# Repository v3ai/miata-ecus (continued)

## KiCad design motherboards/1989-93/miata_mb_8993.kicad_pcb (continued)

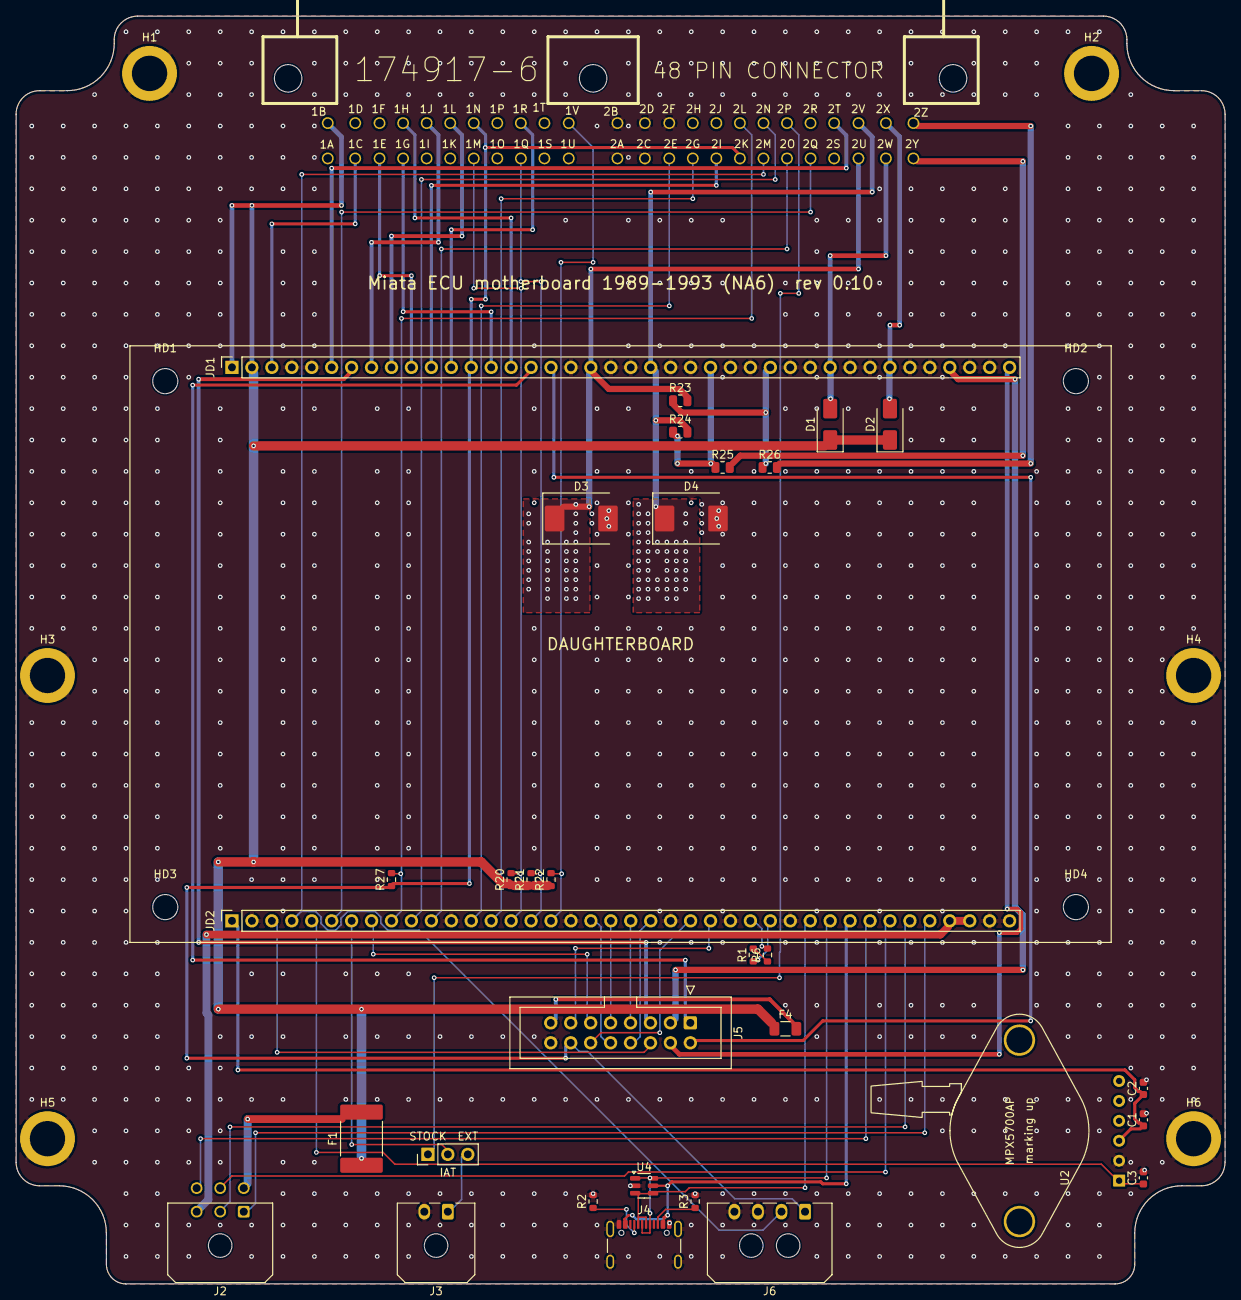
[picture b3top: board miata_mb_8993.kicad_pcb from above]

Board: 2 copper layers, 154.0 x 161.5 mm, 42 parts (0 on the bottom side), 63 nets.

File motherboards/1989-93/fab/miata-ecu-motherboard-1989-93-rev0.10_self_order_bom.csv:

Line,Item,Quantity,Designator,Manufacturer,Manufacture Part Number,LCSC Part Number,Required,Find it,Notes
1,Harness header TE 174917-6,1,J1,TE Connectivity,174917-6,,Yes,https://www.digikey.com/en/products/result?keywords=174917-6,Not available from TE: salvage from a stock NA ECU or buy a clone
2,"Female socket 1x40, 2.54mm, through-hole, 8.5mm",2,"JD1,JD2",Ckmtw(Shenzhen Cankemeng),B-2200S40P-A120,C124412,Yes,https://www.lcsc.com/product-detail/C124412.html,
3,"IDC box header 2x8 (16P), 2.54mm, through-hole",1,J5,BOOMELE(Boom Precision Elec),2.54-2*8P,C3406,Yes,https://www.lcsc.com/product-detail/C3406.html,
4,"Jumper shunt, 2.54 mm",1,,BOOMELE(Boom Precision Elec),2.54 Short Circuit Cap,C5305,Yes,https://www.lcsc.com/product-detail/C5305.html,"For JP1 (IAT source): EXT = board IAT connector J3, STOCK = harness sensor"
5,"Micro-Fit 3.0 header, 1x2 (2P), 3.0mm, right angle, through-hole",1,J3,MOLEX,436500202,C587650,Yes,https://www.lcsc.com/product-detail/C587650.html,
6,"Micro-Fit 3.0 header, 1x4 (4P), 3.0mm, right angle, through-hole",1,J6,MOLEX,436500400,C277684,Yes,https://www.lcsc.com/product-detail/C277684.html,
7,"Micro-Fit 3.0 header, male, 2x3 (6P), 3.0mm, right angle, through-hole",1,J2,MOLEX,430450600,C127367,Yes,https://www.lcsc.com/product-detail/C127367.html,
8,"Pin header, male, 1x3, 2.54mm, through-hole, vertical",1,JP1,BOOMELE(Boom Precision Elec),2.54-1*3PPin,C49257,Yes,https://www.lcsc.com/product-detail/C49257.html,
9,"Pressure sensor 15-700kPa absolute, 5V, ratiometric analog out, unibody single port (867B)",1,U2,NXP,MPX5700AP,C90152,Yes,https://www.lcsc.com/product-detail/C90152.html,"Lies flat, marking side up, leads bent 90 deg down, held by 2 x M3 screws"
10,"Nut, M3",2,,,M3 hex nut,,Yes,,MAP sensor (U2) hold-down
11,"Screw, M3 x 10, pan head",2,,,M3 x 10 pan head,,Yes,,MAP sensor (U2) hold-down
12,"Screw, M3 x 6, pan head",8,,,M3 x 6 pan head,,Yes,,Two per daughterboard standoff (HD1-HD4)
13,"Standoff, M3 x 11 mm, hex, female-female",4,"HD1,HD2,HD3,HD4",,M3 x 11 F-F hex standoff,,Yes,,Daughterboard above the motherboard (8.5 mm sockets + 2.5 mm header plastic)
14,Thick film resistor 0 ohm 0805,2,"R25,R26",UNI-ROYAL(Uniroyal Elec),0805W8F0000T5E,C17477,Optional,https://www.lcsc.com/product-detail/C17477.html,"R25: sequential conversion only, INJ3 to 2Y (fit instead of R24); R26: sequential conversion only, INJ4 to 2Z (fit instead of R23). NEVER on an automatic: 2Z is the A/T unit"
15,Thick film resistor 4.7k 1% 100mW 0603,4,"R20,R21,R22,R27",UNI-ROYAL(Uniroyal Elec),0603WAF4701T5E,C23162,Optional,https://www.lcsc.com/product-detail/C23162.html,"R20: 12 V pull-up for the vehicle speed input. Fit (4.7k 0603, LCSC C23162: 48 mW at 15 V with the switch closed) only if your car's signal switches to ground or is open collector; a switch that drives 12 V must not have it; R21: 12 V pull-up for the A/C switch input. Fit (4.7k 0603, LCSC C23162: 48 mW at 15 V with the switch closed) only if your car's signal switches to ground or is open collector; a switch that drives 12 V must not have it; R22: 12 V pull-up for the clutch switch input. Fit (4.7k 0603, LCSC C23162: 48 mW at 15 V with the switch closed) only if your car's signal switches to ground or is open collector; a switch that drives 12 V must not have it; R27: 5 V pull-up for the TPS idle switch on 2L (manual cars). Fit (4.7k 0603, LCSC C23162; 1.1 mA with the switch closed) if the idle switch is used; from the protected harness 5 V"
16,"Throttle position sensor, 0-5 V potentiometer, 3 pins",1,,Bosch,0 280 122 001,,Manual cars,https://www.digikey.com/en/products/result?keywords=0%20280%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,"Same part as BMW 13 63 1 721 456; the sensor the NA6 adapter plates below are made for. 86 deg usable travel, 2 kOhm track, -40 to +130 C. Pins 1 and 2 are the ends of the track (5 V and ground, about 2 kOhm between them at any throttle), pin 3 the wiper (signal): check with an ohmmeter before wiring. Replaces the stock idle switch"
17,TPS adapter plate for the NA6 throttle body (buy),1,,Flyin' Miata,"TPS upgrade kit 07-360XX, no-TPS option",,Manual cars,https://flyinmiata.com/products/tps-upgrade,Bolts to the side of the 1990-93 manual throttle body and carries the Bosch / BMW sensor. Either this or the printed plate below. Not with an NB intake manifold
18,"TPS plug, Bosch Junior Timer 3-pin, with terminals",1,,Bosch,1 237 000 039,,Manual cars,https://www.efihardware.com/products/388/connector-TPS-Modul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,Mates with the Bosch 0 280 122 001. Buy it as a kit with its terminals (e.g. EFI Hardware C03F-0002): loose terminals often don't fit the housing
19,"Shielded cable, 3 x 22 AWG with drain, 105 C or better",3,,,"M27500-22SB3T23 (or equivalent), metres",,Manual cars,,J6 to the sensor: about 3 m from the ECU in the passenger footwell through the firewall to the throttle body; measure your route. Shield drain to J6 pin 4 only (open at the sensor end). Office cable rated 60 C is not good enough under the hood. Three twisted 22 AWG TXL wires in loom also work (leave pin 4 empty)
20,"Micro-Fit 3.0 receptacle, 1x4",1,,Molex,43645-0400,,Manual cars,https://www.digikey.com/en/products/result?keywords=43645-0400,"Mates with J6: 1 = 5 V, 2 = TPS signal, 3 = sensor ground, 4 = shield drain"
21,"Micro-Fit 3.0 female crimp terminal, 20-24 AWG (TPS lead)",4,,Molex,43030-0007,,Manual cars,https://www.digikey.com/en/products/result?keywords=43030-0007,For the J6 receptacle; buy spares
22,TPS adapter plate for the NA6 throttle body (3D print),1,,,Thingiverse 4476762 or Printables 619337,,Optional,https://www.thingiverse.com/thing:4476762,"Instead of the bought plate: Skuzzle's ""Mazda MX5 - BMW TPS adapter"" (Thingiverse 4476762), or its thicker remix ""BMW tps adaptor maximum beef"" (Printables 619337). Print in ASA (PLA and PETG soften in the engine bay); check the licence on the model page"
23,"Screw, M4, with nut (sensor to printed plate)",2,,,"M4 screw + M4 nut, length to suit the plate",,Optional,,Printed plate only
24,"Screw, M4, with wide (fender) washer (printed plate to throttle body)",2,,,"M4 screw + M4 fender washer, length to suit",,Optional,,Printed plate only: the wide washers spread the load on the plastic
25,"Convoluted loom, 6 mm (1/4 in), split",2,,,"6 mm split loom, metres",,Optional,,"Engine-bay run of the TPS lead; tie it to the engine harness, away from the exhaust and the coil leads"

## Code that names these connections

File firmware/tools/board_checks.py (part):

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Datasheet limits used (STM32F407 DS8626, STM32F103x8 DS5319; F4 family IINJ table re-confirmed in the STM32F412
datasheet, same structure):
  FT pins: VIN abs max VDD + 4.0 V; injected current -5 / +0 mA (no positive injection possible: there is no clamp
  to VDD, so the limit above VDD is the voltage, not a current). TTa (PA4/PA5) and F103 non-FT pins: VIN abs max
  4.0 V, injected current +-5 mA (diodes to VDDA / VDD). Total injected current +-25 mA. Operating range on FT pins
  -0.3..5.5 V. An FT pin used as an ADC input is treated as good to VDDA only (outside it the reading clips; tolerance
  above VDDA in analog mode is not relied on: CHECK).
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F407_NAME = {int(n): name for n, name in
             (s.split(':') for s in open(os.path.join(SCRIPTS, 'stm32f407v_lqfp100_pins.txt')).read().split())}
F407_PIN = {v: k for k, v in F407_NAME.items()}
# DS8626 pin definitions, LQFP100: every GPIO is FT except PA4/PA5 (TTa, DAC outputs); PC13-15 are FT but sit in the
# backup domain (2 MHz, 3 mA total sink/source through the power switch).
F407_TTA = {'PA4', 'PA5'}
F103_NAME = {1: 'VBAT', 2: 'PC13', 3: 'PC14', 4: 'PC15', 5: 'PD0', 6: 'PD1', 7: 'NRST', 8: 'VSSA', 9: 'VDDA',
             10: 'PA0', 11: 'PA1', 12: 'PA2', 13: 'PA3', 14: 'PA4', 15: 'PA5', 16: 'PA6', 17: 'PA7', 18: 'PB0',
             19: 'PB1', 20: 'PB2', 21: 'PB10', 22: 'PB11', 23: 'VSS', 24: 'VDD', 25: 'PB12', 26: 'PB13', 27: 'PB14',
             28: 'PB15', 29: 'PA8', 30: 'PA9', 31: 'PA10', 32: 'PA11', 33: 'PA12', 34: 'PA13', 35: 'VSS', 36: 'VDD',
             37: 'PA14', 38: 'PA15', 39: 'PB3', 40: 'PB4', 41: 'PB5', 42: 'PB6', 43: 'PB7', 44: 'BOOT0', 45: 'PB8',
             46: 'PB9', 47: 'VSS', 48: 'VDD'}
# DS5319 pin definitions: FT = PA8-PA15, PB2-PB4, PB6-PB15, PD0/PD1; not FT: PA0-PA7, PB0, PB1, PB5, PC13-PC15
F103_FT = {'PA8', 'PA9', 'PA10', 'PA11', 'PA12', 'PA13', 'PA14', 'PA15', 'PB2', 'PB3', 'PB4', 'PB6', 'PB7', 'PB8',
           'PB9', 'PB10', 'PB11', 'PB12', 'PB13', 'PB14', 'PB15', 'PD0', 'PD1'}
VDD = 3.3
LIM_FT_V = VDD + 4.0          # abs max on FT pins
LIM_NONFT_V = 4.0             # abs max on TTa / non-FT pins
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FT_OPER_MAX = 5.5
VIL, VIH = 0.3 * VDD, 0.7 * VDD   # DS8626 CMOS levels (conservative; FT inputs switch at 1.79 V by design)

ADC = {**{f'EFI_ADC_{i}': f'PA{i}' for i in range(8)}, 'EFI_ADC_8': 'PB0', 'EFI_ADC_9': 'PB1',
       **{f'EFI_ADC_{10 + i}': f'PC{i}' for i in range(6)}}

# alternate functions whose direction matters (DS8626 / DS5319 alternate-function tables)
AF_DIR = {('U1', 'PB12'): ('CAN2_RX', 'in'), ('U1', 'PB13'): ('CAN2_TX', 'out'),
          ('U1', 'PC6'): ('USART6_TX', 'out'), ('U1', 'PC7'): ('USART6_RX', 'in'),
          ('U1', 'PD8'): ('USART3_TX', 'out'), ('U1', 'PD9'): ('USART3_RX', 'in'),
          ('U102', 'PA9'): ('USART1_TX', 'out'), ('U102', 'PA10'): ('USART1_RX', 'in'),
          ('U102', 'PA11'): ('CAN_RX', 'in'), ('U102', 'PA12'): ('CAN_TX', 'out')}


def mcu_pin_info(ref, pad):
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    'vehicleSpeedSensorInputPin': 'vss', 'acSwitch': 'acSwitch', 'clutchDownPin': 'clutch',
    'tps1_1AdcChannel': 'tps', 'mafAdcChannel': 'maf', 'afr.hwChannel': 'afr', 'ignKeyAdcChannel': 'ignKey',
    'vbattAdcChannel': 'vbatt', 'clt.adcChannel': 'clt', 'iat.adcChannel': 'iat', 'map.sensor.hwChannel': 'map',
    'canTxPin': 'can2Tx', 'canRxPin': 'can2Rx',   # PB13/PB12 = CAN2 peripheral, rusEFI's first bus
}
FW_OUTPUTS = {'ign1&4', 'ign3(COP)', 'ign2&3', 'ign4(COP)', 'inj1', 'inj2', 'inj3', 'inj4', 'idle', 'fuelPump',
              'acRelay', 'fan', 'fan2', 'cel', 'tach', 'boost', 'mainRelay', 'alternator', 'vvt', 'o2heater'}
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    wb = open(os.path.join(BOARD, 'wideband_uart_flash.cpp')).read()
    for label, port in re.findall(r'efiSetPadMode\("WBO ([\w ]+)", Gpio::(\w+)', wb):
        board['wbo ' + label] = 'P' + port
    board['usbDM'], board['usbDP'], board['swdio'], board['swclk'] = 'PA11', 'PA12', 'PA13', 'PA14'
    board['uart6Tx'], board['uart6Rx'] = 'PC6', 'PC7'   # rusEFI's TS secondary / AUX UART (J5-12/13)
    return out, board, sorted(external)


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                      'o2heater', 'vvt', 'boost', 'vss', 'acSwitch', 'clutch'):
                fw[k] = kv.get(k, '-')
            fw = {k: ('P' + v if not v.startswith('P') else v) for k, v in fw.items() if v not in ('-', '')}
            if kv.get('ignKey', '-') not in ('-', ''):      # the dump names the ADC channel ("VIGN"), which is PA2
                fw['ignKey'] = 'PA2'
            out[parts[1]] = fw
    return out

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        row('FAIL', 'mating', year, f'{mb_path}: ' + '; '.join(bad[:6]))
    else:
        row('OK', 'mating', year, f'{mb_path}: all {len(dj)} J1/J2 pads land on JD1/JD2 by pure translation '
            f'({ox:.2f}, {oy:.2f} mm), same pin and net (HTR_GND -> motherboard GND by design)')


# ------------------------------------------------------------------------------------------------------------------
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    has_key = 'ignKey' in fw
    want = exp_tab.get('ignKey')
    ok = (has_key and want in vign_cav) or (not has_key and not want)
    row('OK' if ok else 'FAIL', 'reverse', year, f'ignition sense {"PA2 (AN_VIGN)" if has_key else "not configured"}; '
        f'VIGN_IN cavities wired {vign_cav or "-"}; reference {want or "none"}')
    # unused F407 GPIO with a harness path but no firmware function (informational)
    for pad, net in sorted(sysm.by_ref['U1']['pads'].items(), key=lambda kv: int(kv[0])):
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    """two drivers on one net (push-pull + anything, open drain + car output); intentional open-drain pairs."""
    res = research.get(RESEARCH_YEAR.get(year, ''), {})
    out_ports = {p for f, p in fw.items() if f in FW_OUTPUTS} | {board_fw[k] for k in board_fw if k.startswith('led')} \
        | {board_fw['wbo BOOT0'], 'PB13', 'PC6', 'PD8'}
    od_ports = {board_fw['drvEnable'], board_fw['wbo NRST']}
    drv = collections.defaultdict(list)    # net -> [(who, kind)]  kind: pp / od
    for p in sysm.parts:
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                    drv[net].append((f'U1 {name}', 'pp'))
            elif ref == 'U102':
                name = mcu_pin_info('U102', pad)[0]
                if name in ('PA6', 'PB10', 'PB5', 'PB6', 'PB7', 'PB8', 'PB9', 'PA9', 'PA12'):
                    drv[net].append((f'U102 {name}', 'pp'))
            elif val == 'ULN2003AD' and pad in ('10', '11', '12', '13', '14', '15', '16'):
                drv[net].append((f'{ref}.{pad}', 'od'))
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                   '5': ('+5V', 'ADJ reference')},
    'LMR14020': {'3': ('+12V_F', 'EN (tie to VIN or divider)'), '7': ('GND', 'GND'), '9': ('GND', 'exposed pad')},
    'SN74LVC4245APWR': {'2': ('GND', 'DIR: low = B->A'), '22': ('DRV_EN_N', 'OE')},
    'STM32F407VGT6': {'94': ('BOOT0', 'BOOT0 pulled down'), '37': ('BOOT1', 'PB2/BOOT1 pulled down'),
                      '20': ('GND', 'VSSA'), '21': ('+3V3A', 'VREF+'), '22': ('+3V3A', 'VDDA'),
                      '49': ('VCAP1', 'VCAP1'), '73': ('VCAP2', 'VCAP2'), '6': ('+3V3', 'VBAT')},
    'STM32F103C8T6': {'1': ('+3V3', 'VBAT'), '8': ('GND', 'VSSA'), '9': ('WB_VDDA', 'VDDA'), '44': ('WB_BOOT0', 'BOOT0'),
                      '20': ('WB_BOOT1', 'PB2/BOOT1')},
    'SN65HVD230DR': {'8': ('GND', 'Rs: GND = high speed (open would be standby? low-power mode)')},
    'TCAN1042VDRQ1': {'3': ('+5V', 'VCC 4.5-5.5 V'), '5': ('+3V3', 'VIO = MCU I/O level'),
                      '8': ('GND', 'STB: low = normal mode (internal pull-up would select standby)'), '2': ('GND', 'GND')},
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    ('LM2903DR', ['2', '3', '5', '6'], 'LM2903 input', True, 'unused VR channel must sit at a defined level'),
    ('LMV321IDBVR', ['1', '3'], 'LMV321 input', True, 'knock amp bias'),
    ('STM32F407VGT6', ['94', '37'], 'F407 BOOT0/BOOT1', True, 'boot mode'),
    ('STM32F103C8T6', ['44', '20'], 'F103 BOOT0/BOOT1', True, 'boot mode (BOOT0 is driven by the F407 PD10, high-Z in reset)'),
]


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        relay = [c for c, n in sysm.cavity.items() if n == 'OUT_MAINRLY' and c not in year_unwired(year)]
        txt = f'ignition wake: {vi} -> D8 -> F1: +12V {V["+12V"]:.2f} V with the main relay open'
        if hold:
            txt += f'; firmware holds the main relay on {relay} ({hold}) and reads the key on PA2'
        row('OK' if V['+12V'] > 12 else 'FAIL', 'power', year, txt)
    elif fw.get('mainRelay'):
        row('FAIL', 'power', year, 'firmware drives a main relay but no ignition wake cavity is wired')
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    dc.fix('_HALF', 1.65)
    dc.fix('_MAP', 0.85)
    out_ports = {p for f, p in fw.items() if f in FW_OUTPUTS} | {board_fw[k] for k in board_fw if k.startswith('led')} \
        | {board_fw['wbo BOOT0'], 'PB13', 'PC6', 'PD8'}
    for p in sysm.parts:
        ref, val, pads, fp = p['ref'], p['value'], p['pads'], p['fp']
        base = ref.split('.')[-1]
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                    dc.d(net, vdd, 0.5, 10, tag=('MCU+', ref, k))
                if ref == 'U1' and name in out_ports:
                    dc.r(net, '+3V3' if states.get(f'U1.{name}') == 'high' else 'GND', 40, tag=('MCU_OUT', ref, k))
                if ref == 'U102' and name == 'PB10':
                    dc.r(net, 'GND', 40)
                if ref == 'U102' and name == 'PA6':
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
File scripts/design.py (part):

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J1 = {1: 'VBAT_IN', 2: 'VBAT_IN', 3: 'VIGN_IN', 4: 'GND', 5: 'GND',
      6: 'OUT_FP', 7: 'OUT_MAINRLY', 8: 'OUT_AC', 9: 'OUT_FAN', 10: 'OUT_CEL',
      11: 'OUT_TACH', 12: 'OUT_LS7',
      # rev 0.8: pin 13 (was GND) carries the harness sensor 5 V (V5_EXT, its own protected tracker U14), so a
      # harness 5 V wire shorted to battery no longer back-feeds the on-board MAP sensor (V5_SENS, J2-1)
      13: 'V5_EXT',
      14: 'OUT_IGN1', 15: 'OUT_IGN2', 16: 'OUT_IGN3', 17: 'OUT_IGN4', 18: 'GND'}
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    '21': '+3V3A', '22': '+3V3A',
    '49': 'VCAP1', '73': 'VCAP2',
    '12': 'HSE_IN', '13': 'HSE_OUT', '14': 'NRST', '94': 'BOOT0',
    # relay/lamp outputs from the top of the left edge (ULN2003 sits up-left). PC13/PC14 run through the backup
    # power switch, which can supply 3 mA in total; the two ULN2003 inputs draw at most ~0.72 mA each at 3.3 V
    # ((3.3 - 2 Vbe) / 2.7k), so 1.45 mA together, and relays need no speed (ST's limit there is 2 MHz).
    '1': 'LS7_CTL', '2': 'TACH_CTL', '3': 'CEL_CTL', '4': 'FAN_CTL', '5': 'AC_CTL',
    '7': 'MAINRLY_CTL', '8': 'FP_CTL',
    # rev 0.5: PB2 is BOOT1; pulled low so ST's DFU bootloader starts reliably (BOOT0 = 1, BOOT1 = 0)
    '37': 'BOOT1',
    # rev 0.5: low-side driver enable (PA8, active low, pulled up to +5V: drivers off until firmware enables).
    # On the right edge, so it reaches U11's ~OE from below instead of adding a ninth line to the top-edge bundle.
    '67': 'DRV_EN_N',
    # ignition + smart low sides from the top edge, ordered left->right like the driver row
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    '93': 'INJ1_CTL', '92': 'INJ2_CTL', '91': 'INJ3_CTL', '90': 'INJ4_CTL',
    '89': 'IACV_CTL', '88': 'VVT_CTL', '87': 'BOOST_CTL', '86': 'ALT_CTL',
    # analog: all nine sensor inputs on the bottom edge in J2 column order, knock on
    # PA3 (ADC3_IN3); battery/ignition sense on the left edge next to their divider
    '26': 'AN_KNOCK', '29': 'AN_TPS', '30': 'AN_MAP', '31': 'AN_CLT', '32': 'AN_IAT',
    '33': 'AN_AFR', '34': 'AN_AUX1', '35': 'AN_AUX2', '36': 'AN_AUX3',
    '24': 'AN_VBATT', '25': 'AN_VIGN',
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    '38': 'HALL1', '39': 'HALL2', '40': 'SW1', '41': 'SW2', '42': 'SW3',
    '43': 'VR2_OUT', '44': 'VR1_OUT',
    # comms (right edge)
    '51': 'CAN_RX', '52': 'CAN_TX',            # CAN2 PB12/PB13
    # rev 0.10: PC6 / PC7 are the flex-fuel sensor and nitrous arming inputs (they were a spare UART); same 10k + clamps
    '63': 'FLEX_M', '64': 'N2O_ARM_M',
    # rev 0.10: microSD on SPI2 (PB10 SCK, PB14 MISO, PB15 MOSI; CS on PD13)
    '47': 'SD_SCK', '53': 'SD_MISO', '54': 'SD_MOSI', '60': 'SD_CS',
    # LEDs: run PD12, error PD15; rev 0.8 moved comms and warning to PC8/PC9 (PD13/PD14 left no route to the LED column)
    '59': 'LED_RUN', '65': 'LED_COMM', '66': 'LED_WARN', '62': 'LED_ERR',
    # wideband MCU programming link (rev 0.4): USART3 on PD8/PD9 to the wideband MCU's ROM-bootloader USART1 (F103 since rev 0.6)
    # (PA10/PA9), PD10 drives its BOOT0 (10k pull-down stays), PD11 (open drain) its NRST
    '55': 'WB_PROG_TX', '56': 'WB_PROG_RX', '57': 'WB_BOOT0', '58': 'WB_NRST',
    '70': 'USB_DM', '71': 'USB_DP',            # OTG_FS PA11/PA12
    '72': 'SWDIO', '76': 'SWCLK',              # PA13/PA14
}
add('U1', 'STM32F407VGT6', 'LQFP100', 'C12345', mcu, 'MCU, 168MHz Cortex-M4F, 1MB flash')

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    R(f'R{rn}', '10k', 'AN_' + n, 'GND', '0402'); rn += 1
    C(f'C{cn}', '10n', 'AN_' + n, 'GND', '0402'); cn += 1
    if n in ('CLT', 'IAT'):     # rev 0.8: bias from the harness sensor supply V5_EXT (the sensors are harness parts)
        R(f'R{rn}', '2.7k', 'V5_EXT', 'IN_' + n, '0603'); rn += 1

# knock: AC coupled, biased to 1.65V, gain 5.7. Rev 0.7: the coupling cap follows R138 (2.2k, see the rev 0.7 block)
C(f'C{cn}', '100n', 'KN_IN', 'KN_P'); cn += 1
R(f'R{rn}', '100k', 'KN_P', 'KN_BIAS'); rn += 1
R(f'R{rn}', '100k', '+3V3', 'KN_BIAS'); rn += 1
R(f'R{rn}', '100k', 'KN_BIAS', 'GND'); rn += 1
C(f'C{cn}', '1u', 'KN_BIAS', 'GND'); cn += 1
R(f'R{rn}', '47k', 'KN_OUT', 'KN_N'); rn += 1
R(f'R{rn}', '10k', 'KN_N', 'KN_BIAS'); rn += 1
R(f'R{rn}', '330', 'KN_OUT', 'AN_KNOCK'); rn += 1
C(f'C{cn}', '10n', 'AN_KNOCK', 'GND'); cn += 1
C(f'C{cn}', '100n', '+3V3', 'GND'); cn += 1
add('U8', 'LMV321IDBVR', 'SOT235', 'C7972',
    {'1': 'KN_P', '2': 'GND', '3': 'KN_N', '4': 'KN_OUT', '5': '+3V3'}, 'knock amp')
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# 2 x 5.1k to the comparator inputs, 1 nF across them, a BAT54S on each input to GND and +5V (holds them at -0.3..5.3 V;
# the LM2903 inputs take up to 36 V and down to -0.3 V), 100k from each input to VBIAS (1.65 V), and 1M from the
# open-collector output back to IN+ for about 30 mV of hysteresis. Output high when harness - is above harness +
# (the MAX9926's polarity), 10k pull-up to +3V3 into PE13/PE12. See firmware/tools/circuit_sim.py section H.
# comparator A (pins 1-3) takes VR2 and B (5-7) VR1, so each channel's pins face its own header columns
add('U9', 'LM2903DR', 'SOIC8', 'C7549',
    {'1': 'VR2_OUT', '2': 'VR2_INN', '3': 'VR2_INP', '4': 'GND',
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    R(f'R{rn}', '4.7k', 'IN_' + n, n, '0603'); rn += 1
    R(f'R{rn}', '1k', f'V5_H{k + 1}', 'IN_' + n, '0603'); rn += 1
    C(f'C{cn}', '1n', n, 'GND', '0402'); cn += 1
# rev 0.5: clamp diodes to +3V3 (PE7/PE8 are 5 V-tolerant pins with no clamp of their own; a crank/cam wire
# shorted to battery would otherwise put ~14 V on them). 4.7k limits the clamp current to ~2 mA.
add('D13', '1N4148WS', 'SOD323', 'C2128', {'1': '+3V3', '2': 'HALL1'}, 'HALL1 clamp to +3V3')
add('D14', '1N4148WS', 'SOD323', 'C2128', {'1': '+3V3', '2': 'HALL2'}, 'HALL2 clamp to +3V3')
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C('C57', '100n', '+5V', 'GND', '0402')        # U11 VCCA
C('C58', '100n', '+3V3', 'GND', '0402')       # U11 VCCB
R('R71', '10k', '+5V', 'DRV_EN_N', '0402')    # drivers disabled until the firmware pulls DRV_EN_N low
R('R72', '10k', 'BOOT1', 'GND', '0402')       # PB2 / BOOT1 low
# The MCU-side control lines have no pull-downs (no room between the MCU and U11). While U11 is disabled its
# outputs are high-impedance and R19-R26 hold the drivers off, so a floating MCU pin does nothing. Once enabled,
# the board firmware parks every control pin rusEFI isn't using as an input with pull-down (rusEFI's own
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# AUX header UART (J2 24/25 -> motherboard J5): 10k in series and a BAT54S clamp at the MCU side, so the header pins
# survive car wiring shorted to battery (about 55 mW in the resistor at 24 V; 4.7k took 120 mW, over the 0603's 100 mW);
# 10k + ~50 pF of header and cable is 0.5 us, fine at 115200 baud (8.7 us per bit)
# Rev 0.10: the two pins are general 0-12 V digital inputs now: flex-fuel sensor (PC6, EXTI line 6 is free; PC7 would
# share line 7 with the crank input on PE7) and the nitrous arming switch (PC7, polled). Pull-ups are on the motherboard.
R('R139', '10k', 'FLEX_M', 'IN_FLEX')
R('R140', '10k', 'N2O_ARM_M', 'IN_N2O')
add('D36', 'BAT54S', 'SOT23', 'C19726', {'1': 'GND', '2': '+3V3', '3': 'FLEX_M'}, 'flex input clamp')
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R('R161', '47k', '+3V3', 'SD_MOSI', '0402')
R('R162', '47k', '+3V3', 'SD_DAT1', '0402')
R('R163', '47k', '+3V3', 'SD_DAT2', '0402')
# battery / ignition sense clamps: in a 24 V jump start the divider put 4.0 V on PA1 (analog mode, VDDA + 0.3 V max)
add('D38', 'BAT54WS', 'SOD323', 'C124205', {'1': '+3V3', '2': 'AN_VBATT'}, 'AN_VBATT clamp to +3V3')
add('D39', 'BAT54WS', 'SOD323', 'C124205', {'1': '+3V3', '2': 'AN_VIGN'}, 'AN_VIGN clamp to +3V3')
# +3V3 shunt clamp: every clamp on the board (analog, hall, switch, UART, the wideband's pump/Vm drive) dumps a fault
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
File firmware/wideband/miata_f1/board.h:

/*
    ChibiOS - Copyright (C) 2006..2018 Giovanni Di Sirio

    Licensed under the Apache License, Version 2.0 (the "License");
    you may not use this file except in compliance with the License.
    You may obtain a copy of the License at

        http://www.apache.org/licenses/LICENSE-2.0

    Unless required by applicable law or agreed to in writing, software
    distributed under the License is distributed on an "AS IS" BASIS,
    WITHOUT WARRANTIES OR CONDITIONS OF ANY KIND, either express or implied.
    See the License for the specific language governing permissions and
    limitations under the License.
*/

#ifndef _BOARD_H_
#define _BOARD_H_

/*
 * Board identifier.
 */
#define BOARD_NAME                  "miata-ecus daughterboard wideband (STM32F103C8)"

/*
 * Board oscillators-related settings.
 * NOTE: LSE not fitted.
 * HSE: 8 MHz crystal Y101.
 */
#if !defined(STM32_LSECLK)
#define STM32_LSECLK                0U
#endif

#if !defined(STM32_HSECLK)
#define STM32_HSECLK                8000000U
#endif

/*
 * MCU type: STM32F103C8T6 / CBT6 (medium density, 64/128 KB flash, 20 KB RAM, LQFP48).
 */
#define STM32F103xB

/*
 * I/O ports initial setup, this configuration is established soon after reset
 * in the initialization code.
 *
 * The digits have the following meaning:
 *   0 - Analog input.
 *   1 - Push Pull output 10MHz.
 *   2 - Push Pull output 2MHz.
 *   3 - Push Pull output 50MHz.
 *   4 - Digital input.
 *   5 - Open Drain output 10MHz.
 *   6 - Open Drain output 2MHz.
 *   7 - Open Drain output 50MHz.
 *   8 - Digital input with PullUp or PullDown resistor depending on ODR.
 *   9 - Alternate Push Pull output 10MHz.
 *   A - Alternate Push Pull output 2MHz.
 *   B - Alternate Push Pull output 50MHz.
 *   C - Reserved.
 *   D - Alternate Open Drain output 10MHz.
 *   E - Alternate Open Drain output 2MHz.
 *   F - Alternate Open Drain output 50MHz.
 * Please refer to the STM32 Reference Manual for details.
 */

/*
 * Port A setup (the analog front end is the rusEFI/FOME wideband module, rev C).
 * PA0  - Un_sense (Nernst, x2.7)   (analog in, ADC12_IN0).
 * PA1  - not connected (rev 0.7; the module wired it to LSU_Vm, never sampled).
 * PA2  - Ip_sense                  (analog in, ADC12_IN2).
 * PA3  - Vm_sense (virtual ground) (analog in, ADC12_IN3).
 * PA4, PA5 - unused                (input, pull-up).
 * PA6  - Ip_dac PWM, TIM3_CH1      (alternate pushpull, 50 MHz).
 * PA7, PA8 - unused                (input, pull-up).
 * PA9  - USART1_TX                 (input, pull-up: only the ROM bootloader uses it, for flashing from the ECU).
 * PA10 - USART1_RX                 (input, pull-up).
 * PA11 - CAN_RX                    (input, pull-up).
 * PA12 - CAN_TX                    (alternate pushpull, 50 MHz).
 * PA13 - SWDIO, PA14 - SWCLK, PA15 - unused (JTDI).
 */
#define VAL_GPIOACRL            0x8B880000      /*  PA7...PA0 */
#define VAL_GPIOACRH            0x888B8888      /* PA15...PA8 */
#define VAL_GPIOAODR            0x0000FFFF

/*
 * Port B setup.
 * PB0  - Vbatt_sense, 100k/10k     (analog in, ADC12_IN8).
 * PB1  - unused                    (input, pull-up).
 * PB2  - BOOT1, 10k to GND (R135)  (input, floating).
 * PB3, PB4 - unused (JTDO, NJTRST) (input, pull-up).
 * PB5  - Nernst 4.2 ESR drive, 6.8k (input, floating: high-Z until selected).
 * PB6  - Nernst ADV ESR drive, 47k (input, floating: high-Z until selected).
 * PB7  - Nernst 4.9 ESR drive, 22k (output pushpull, 50 MHz: the default sensor).
 * PB8  - LED_BLUE                  (output pushpull, 2 MHz, starts off).
 * PB9  - LED_GREEN                 (output pushpull, 2 MHz, starts off).
 * PB10 - heater PWM, TIM2_CH3      (alternate pushpull, 50 MHz; TIM2 partial remap 2, set in boardInit).
 * PB11..PB15 - unused              (input, pull-up).
 */
#define VAL_GPIOBCRL            0x34488480      /*  PB7...PB0 */
#define VAL_GPIOBCRH            0x88888B22      /* PB15...PB8 */
#define VAL_GPIOBODR            0x0000FCFF

/*
 * Port C setup.
 * PC13 - ID_SEL1, PC14 - ID_SEL2   (digital input, not connected: "floating" strap = default CAN index).
 * PC15 - unused                    (input, pull-up). PC0..PC12 are not bonded on LQFP48.
 */
#define VAL_GPIOCCRL            0x88888888      /*  PC7...PC0 */
#define VAL_GPIOCCRH            0x84488888      /* PC15...PC8 */
#define VAL_GPIOCODR            0x0000FFFF

/*
 * Port D setup.
 * PD0, PD1 - OSC_IN / OSC_OUT (crystal).
 */
#define VAL_GPIODCRL            0x88888844      /*  PD7...PD0 */
#define VAL_GPIODCRH            0x88888888      /* PD15...PD8 */
#define VAL_GPIODODR            0x0000FFFF

/*
 * Port E setup (not bonded on LQFP48).
 */
#define VAL_GPIOECRL            0x88888888      /*  PE7...PE0 */
#define VAL_GPIOECRH            0x88888888      /* PE15...PE8 */
#define VAL_GPIOEODR            0x0000FFFF

/*
 * USB bus activation macro, required by the USB driver.
 */
#define usb_lld_connect_bus(usbp)

/*
 * USB bus de-activation macro, required by the USB driver.
 */
#define usb_lld_disconnect_bus(usbp)

#if !defined(_FROM_ASM_)
#ifdef __cplusplus
extern "C" {
#endif
  void boardInit(void);
#ifdef __cplusplus
}
#endif
#endif /* _FROM_ASM_ */

#endif /* _BOARD_H_ */

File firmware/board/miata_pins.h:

/**
 * @file miata_pins.h
 * @brief Pin map of the miata-ecus daughterboard (rev 0.10; rev 0.9 boards run the same firmware: the pins added in
 * rev 0.10 are not connected there). Must match scripts/design.py ("mcu" dict);
 * firmware/tools/check_pins.py cross-checks the two.
 */

#pragma once

// ---------------------------------------------------------------------------------------------------------------
// Pin map (daughterboard rev 0.8; the MCU pins are unchanged since rev 0.5)
// ---------------------------------------------------------------------------------------------------------------
// Ignition: TC4427 5 V push-pull drivers, active high. The stock harness only has IGN1 (coil pack 1&4) and IGN2 (2&3).
// Rev 0.8: each output sources through 100 R + a Schottky and has a protected low-side pull-down (ZXMS6004, gate from
// an inverter), so a coil wire shorted to battery no longer back-drives the TC4427.
#define MIATA_IGN1 Gpio::E1
#define MIATA_IGN2 Gpio::E0
#define MIATA_IGN3 Gpio::B9
#define MIATA_IGN4 Gpio::B8
// Protected low sides, active high: ST VND7NV04 (rev 0.8; NCV8406A in rev 0.5b-0.7, AUIPS2041L before), driven at 5 V
// through an SN74LVC4245A whose output enable is MIATA_DRV_EN (open drain, active low, pulled up to 5 V): all eight
// stay off until the firmware enables them.
#define MIATA_INJ1 Gpio::B7
#define MIATA_INJ2 Gpio::B6
#define MIATA_INJ3 Gpio::B5
#define MIATA_INJ4 Gpio::B4
#define MIATA_IACV Gpio::B3
#define MIATA_VVT Gpio::D7    // NB2 OCV; 1996-97 and NB1 front O2 heater; 1989-93 purge
#define MIATA_BOOST Gpio::D6  // AUX header only
#define MIATA_ALT Gpio::D5    // NB alternator field; 1994-95 pressure regulator solenoid
// Relay / lamp / tach outputs, active high: ZXMS6004 protected low sides (rev 0.8; a ULN2003 before), driven at 5 V
// through a second SN74LVC4245A (U12) on the same MIATA_DRV_EN enable, so they too stay off until the firmware
// enables the drivers.
#define MIATA_FP Gpio::C14      // backup-domain pin: drives a CMOS shifter input (no load; ST's switch limit 3 mA). Also OSC32_IN: the LSE is kept off (board/mcuconf.h)
#define MIATA_MAINRLY Gpio::C13 // 2003-05 main relay; NB1 VICS solenoid
#define MIATA_AC Gpio::E6
#define MIATA_FAN Gpio::E5
#define MIATA_CEL Gpio::E4
#define MIATA_TACH Gpio::E3
#define MIATA_LS7 Gpio::E2      // second fan / condenser fan relay
// Low-side driver enable (PA8): drive low to enable the eight low-side driver inputs.
#define MIATA_DRV_EN Gpio::A8
// Digital inputs.
#define MIATA_HALL1 Gpio::E7    // crank (NA: CAS SGT, NB: CKP), 1k pull-up to the harness 5 V through a Schottky, clamped to 3.3 V
#define MIATA_HALL2 Gpio::E8    // cam (NA: CAS SGC, NB: CMP)
#define MIATA_SW1 Gpio::E9      // 12 V input through 22k/10k (rev 0.8; 33k/10k before): vehicle speed on every motherboard
#define MIATA_SW2 Gpio::E10     // A/C switch
#define MIATA_SW3 Gpio::E11     // clutch switch
// rev 0.10: two more 0-12 V inputs on J2 pins 24/25 (10k in series, clamped to 3.3 V; a spare UART up to rev 0.9).
#define MIATA_FLEX Gpio::C6     // flex-fuel sensor (50-150 Hz). The motherboard pulls the line up to the sensor 5 V (4.7k); 10 us filter
#define MIATA_N2O_ARM Gpio::C7  // nitrous arming switch to 12 V. The motherboard pulls the line down (10k); 100 us filter
// rev 0.10: microSD socket on SPI2 (microRusEFI's arrangement, with the clock on PB10 because PB13 is the CAN transmit pin).
#define MIATA_SD_SCK Gpio::B10
#define MIATA_SD_MISO Gpio::B14
#define MIATA_SD_MOSI Gpio::B15
#define MIATA_SD_CS Gpio::D13
// Analog inputs (0-5 V through 5.6k/10k, so x1.56 at the ADC).
#define MIATA_IN_VBATT EFI_ADC_1   // PA1, 33k/6.8k; rev 0.10: from the battery input itself (up to rev 0.9 after D7 and the fuse, 0.3-0.6 V low)
#define MIATA_IN_VIGN EFI_ADC_2    // PA2, 33k/6.8k
#define MIATA_IN_TPS EFI_ADC_4     // PA4
#define MIATA_IN_MAP EFI_ADC_5     // PA5, on-board MPX5700AP
#define MIATA_IN_CLT EFI_ADC_6     // PA6, 2.7k pull-up to the harness 5 V (V5_EXT, rev 0.8: a second TLS115 tracking +5V)
#define MIATA_IN_IAT EFI_ADC_7     // PA7, 2.7k pull-up; JP1 on the motherboard picks stock or M12 sensor
#define MIATA_IN_AFR EFI_ADC_14    // PC4, external 0-5 V wideband (the on-board one talks CAN)
#define MIATA_IN_AUX1 EFI_ADC_15   // PC5, rear O2 / idle switch / load signal, depending on year
#define MIATA_IN_AUX2 EFI_ADC_8    // PB0, front narrowband O2
#define MIATA_IN_AUX3 EFI_ADC_9    // PB1, AFM flap or MAF signal

// Board voltages and dividers.
static constexpr float MIATA_VBATT_DIVIDER = (33.0f + 6.8f) / 6.8f;
static constexpr float MIATA_ANALOG_DIVIDER = (5.6f + 10.0f) / 10.0f;
// CLT and IAT: 2.7k pull-up to 5 V, and the 5.6k + 10k ADC divider loads the same node. The Thevenin equivalent of
// the two is a 4.26 V supply behind 2.30k, which is exactly the pull-up model rusEFI's thermistor code uses.
static constexpr float MIATA_TEMP_PULLUP = 2700.0f;
static constexpr float MIATA_TEMP_LOAD = 5600.0f + 10000.0f;
static constexpr float MIATA_TEMP_BIAS = MIATA_TEMP_PULLUP * MIATA_TEMP_LOAD / (MIATA_TEMP_PULLUP + MIATA_TEMP_LOAD);
static constexpr float MIATA_TEMP_SUPPLY = 5.0f * MIATA_TEMP_LOAD / (MIATA_TEMP_PULLUP + MIATA_TEMP_LOAD);
